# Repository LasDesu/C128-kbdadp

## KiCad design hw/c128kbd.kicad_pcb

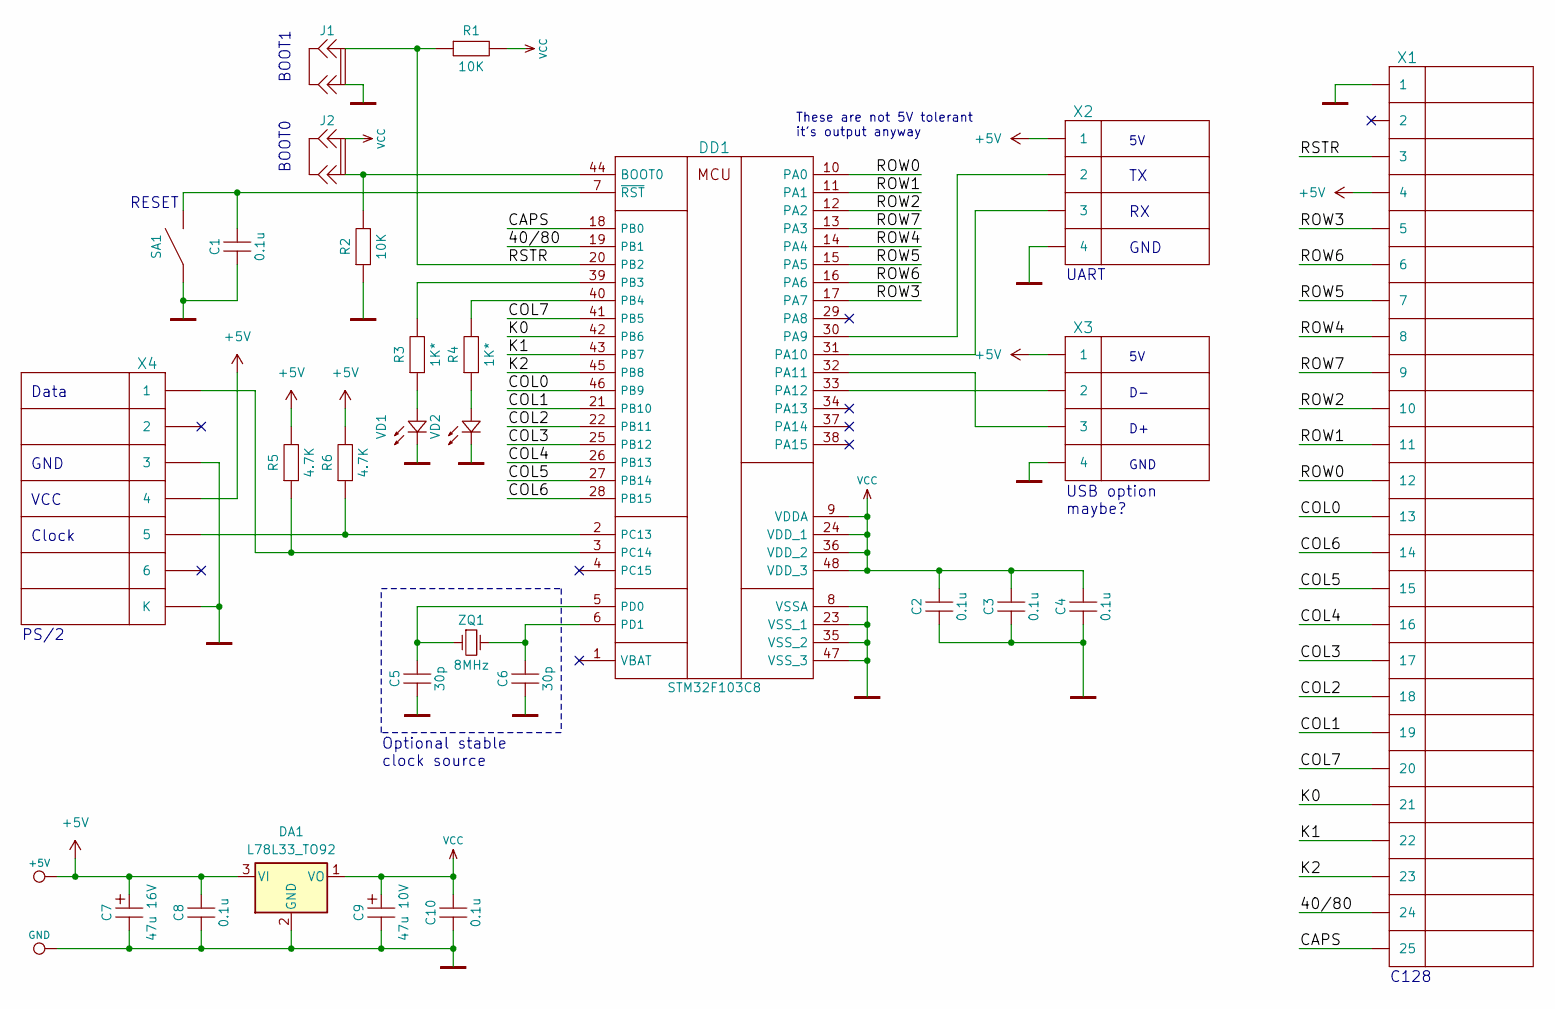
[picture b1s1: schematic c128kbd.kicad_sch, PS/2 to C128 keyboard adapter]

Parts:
C1, C2, C3, C4, C8, C10: 0.1u; C_0805_HandSoldering
C5, C6: 30p; C_0805_HandSoldering
C7: 47u 16V; CP_Radial_D5.0mm_P2.50mm
C9: 47u 10V; CP_Radial_D5.0mm_P2.50mm
DA1: L78L33_TO92; TO-92_Inline_Wide
DD1: STM32F103C8; LQFP-48_7x7mm_Pitch0.5mm
J1, J2: JUMPER2; Pin_Header_Straight_1x02_Pitch2.54mm
P1: +5V; Pin_Header_Straight_1x01_Pitch2.54mm
P2: GND; Pin_Header_Straight_1x01_Pitch2.54mm
R1, R2: 10K; R_0805_HandSoldering
R3, R4: 1K*; R_0805_HandSoldering
R5, R6: 4.7K; R_0805_HandSoldering
SA1: SW_OFF; Pin_Header_Straight_1x02_Pitch2.54mm
VD1, VD2: LED; LED_D3.0mm
X1: CONN-25; DSUB-25_Male_Horizontal_Pitch2.77x2.84mm_EdgePinOffset4.94m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
X2, X3: CONN-4; Socket_Strip_Straight_1x04_Pitch2.54mm
X4: CONN-6S; Mini_din6
ZQ1: 8MHz; Crystal_HC18-U_Vertical

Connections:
+5V: C7.1, C8.2, DA1.3 (VI), P1.1, R5.2, R6.2, X1.4, X2.1, X3.1, X4.4
/40/80: DD1.19 (PB1), X1.24
/CAPS: DD1.18 (PB0), X1.25
/COL0: DD1.46 (PB9), X1.13
/COL1: DD1.21 (PB10), X1.19
/COL2: DD1.22 (PB11), X1.18
/COL3: DD1.25 (PB12), X1.17
/COL4: DD1.26 (PB13), X1.16
/COL5: DD1.27 (PB14), X1.15
/COL6: DD1.28 (PB15), X1.14
/COL7: DD1.41 (PB5), X1.20
/K0: DD1.42 (PB6), X1.21
/K1: DD1.43 (PB7), X1.22
/K2: DD1.45 (PB8), X1.23
/ROW0: DD1.10 (PA0), X1.12
/ROW1: DD1.11 (PA1), X1.11
/ROW2: DD1.12 (PA2), X1.10
/ROW3: DD1.17 (PA7), X1.5
/ROW4: DD1.14 (PA4), X1.8
/ROW5: DD1.15 (PA5), X1.7
/ROW6: DD1.16 (PA6), X1.6
/ROW7: DD1.13 (PA3), X1.9
/RSTR: DD1.20 (PB2), J1.1, R1.1, X1.3
GND: C1.1, C2.1, C3.1, C4.1, C5.1, C6.1, C7.2, C8.1, C9.2, C10.1, DA1.2 (GND), DD1.8 (VSSA), DD1.23 (VSS_1), DD1.35 (VSS_2), DD1.47 (VSS_3), J1.2, P2.1, R2.1, SA1.1, VD1.1, VD2.1, X1.1, X2.4, X3.4, X4.3, X4.S (К)
unnamed: DD1.44 (BOOT0), J2.2, R2.2
unnamed: DD1.30 (PA9), X2.2
unnamed: DD1.31 (PA10), X2.3
unnamed: DD1.32 (PA11), X3.3
unnamed: DD1.33 (PA12), X3.2
unnamed: DD1.39 (PB3), R3.2
unnamed: DD1.40 (PB4), R4.2
unnamed: DD1.2 (PC13), R6.1, X4.5
unnamed: DD1.3 (PC14), R5.1, X4.1
unnamed: C5.2, DD1.5 (PD0), ZQ1.1
unnamed: C6.2, DD1.6 (PD1), ZQ1.2
unnamed: C1.2, DD1.7 (~RST), SA1.2
unnamed: R3.1, VD1.2
unnamed: R4.1, VD2.2
VCC: C2.2, C3.2, C4.2, C9.1, C10.2, DA1.1 (VO), DD1.9 (VDDA), DD1.24 (VDD_1), DD1.36 (VDD_2), DD1.48 (VDD_3), J2.1, R1.2

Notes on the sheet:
PS/2
VCC
BOOT0
UART
GND
C128
Clock
Optional stable clock source
BOOT1
These are not 5V tolerant it's output anyway
RESET
Data
USB option maybe?

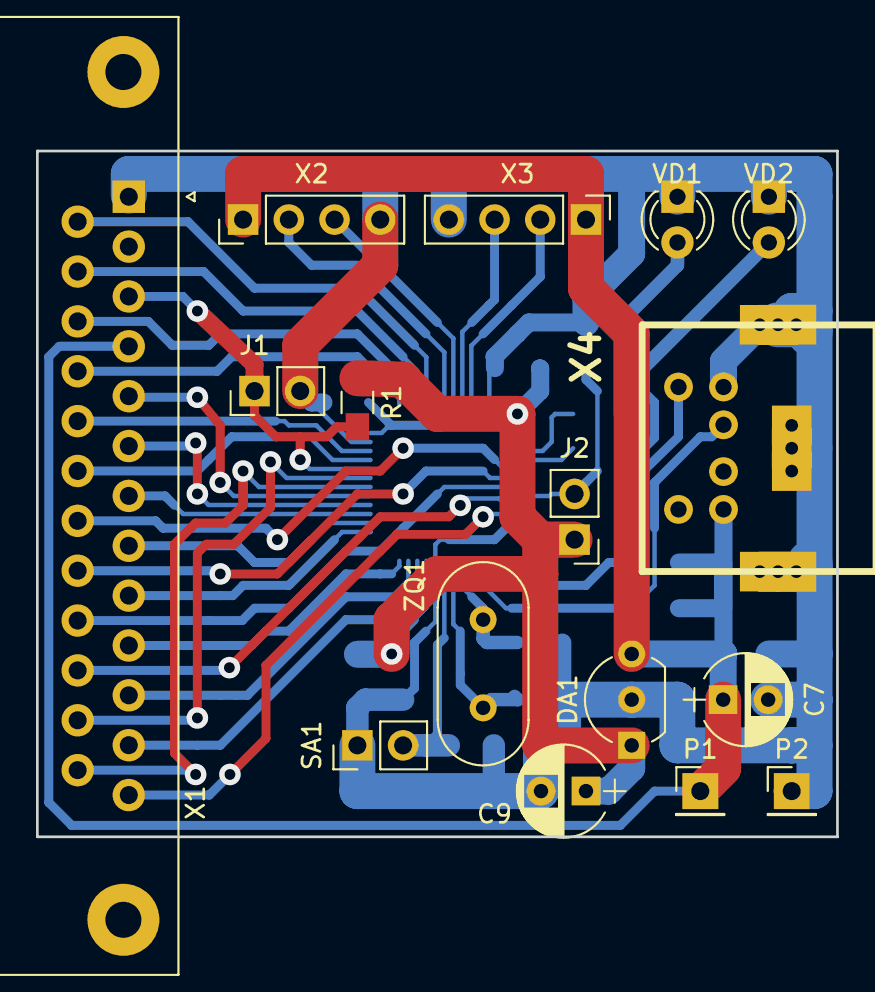
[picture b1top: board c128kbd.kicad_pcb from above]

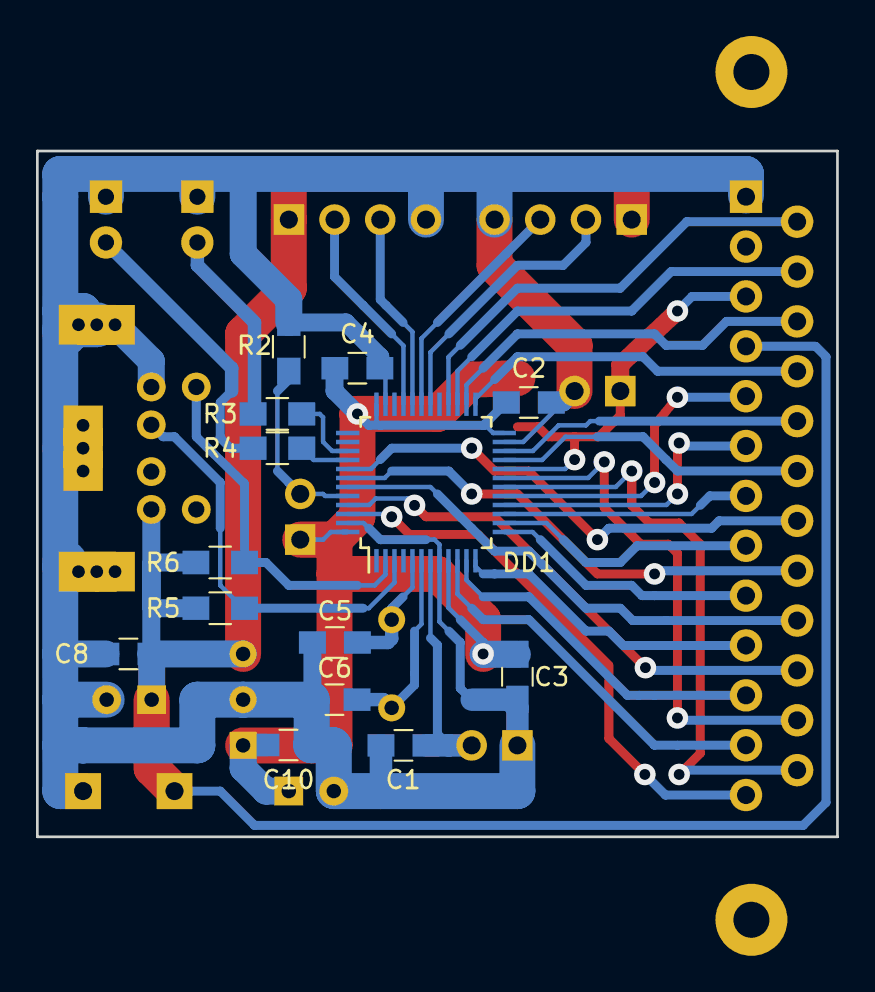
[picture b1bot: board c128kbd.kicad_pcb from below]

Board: 2 copper layers, 44.5 x 38.1 mm, 30 parts (14 on the bottom side), 39 nets.

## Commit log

2018-07-08 Add firmware
2019-08-25 Unfinished new PCB and gerbers used to produce first experimental version
2020-05-31 Fix cursor keys; add C64 cursor key emulation (Num-lock switched, enabled by default)
2020-05-31 More or less final version of hardware
2020-05-31 Cosmetic fixes
2024-09-27 hw: update to kicad 8, should be no problems with cache
